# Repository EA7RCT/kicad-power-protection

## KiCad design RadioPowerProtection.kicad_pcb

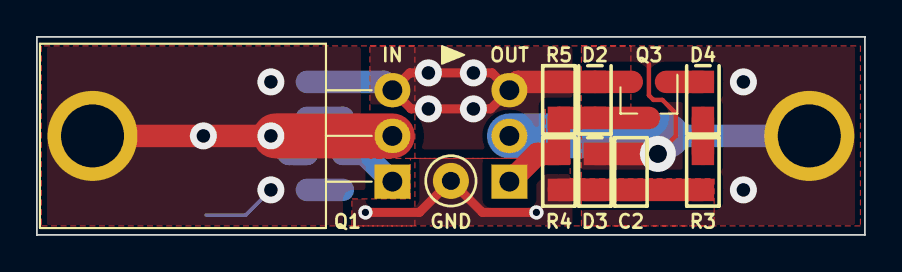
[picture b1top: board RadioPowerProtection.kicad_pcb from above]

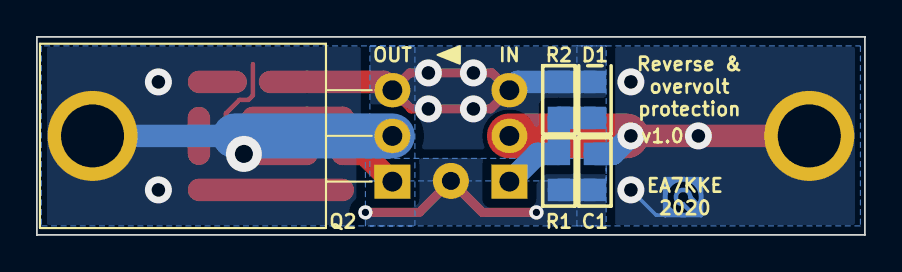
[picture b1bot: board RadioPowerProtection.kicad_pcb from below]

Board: 2 copper layers, 46.0 x 11.0 mm, 16 parts (6 on the bottom side), 8 nets.

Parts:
C1, C2: C; SMD_0805
D1, D2, D4: D_Zener; SMD_0805_Polarized
D3: D; SMD_0805_Polarized
GND: Screw_Terminal_01x01; TestPoint_Keystone_5000-5004_Miniature
Q1, Q2: IRF4905; TO-220-3_Horizontal_TabDown
Q3: Q_PNP_BCE; SOT-23
R1: 0; SMD_0805
R2, R5: 100k; SMD_0805
R3: 1k; SMD_0805
R4: 4k7; SMD_0805
Ref**: andresgongora

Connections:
/PowerBus: D1.1, D2.1, Q1.3, Q2.3, Q3.2, R2.1, R5.1
Earth: C1.2, C2.2, D3.2, GND.1, R1.2, R3.2, R4.2
unnamed: D1.2, Q1.1, R1.1, R2.2
unnamed: D2.2, Q2.1, Q3.3, R4.1, R5.2
unnamed: D4.1, Q3.1
unnamed: D4.2, R3.1
PowerIn: C1.1, Q1.2, Ref**.0
PowerOut: C2.1, D3.1, Q2.2

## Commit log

2020-11-26 Fix PNP transistor
2020-12-28 Update for manufacture
2020-12-29 Add gerbers
